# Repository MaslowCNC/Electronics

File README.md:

# Maslow PCBs

The printed circuit board which powers the Maslow CNC Machine

======================

Layout

Schematic

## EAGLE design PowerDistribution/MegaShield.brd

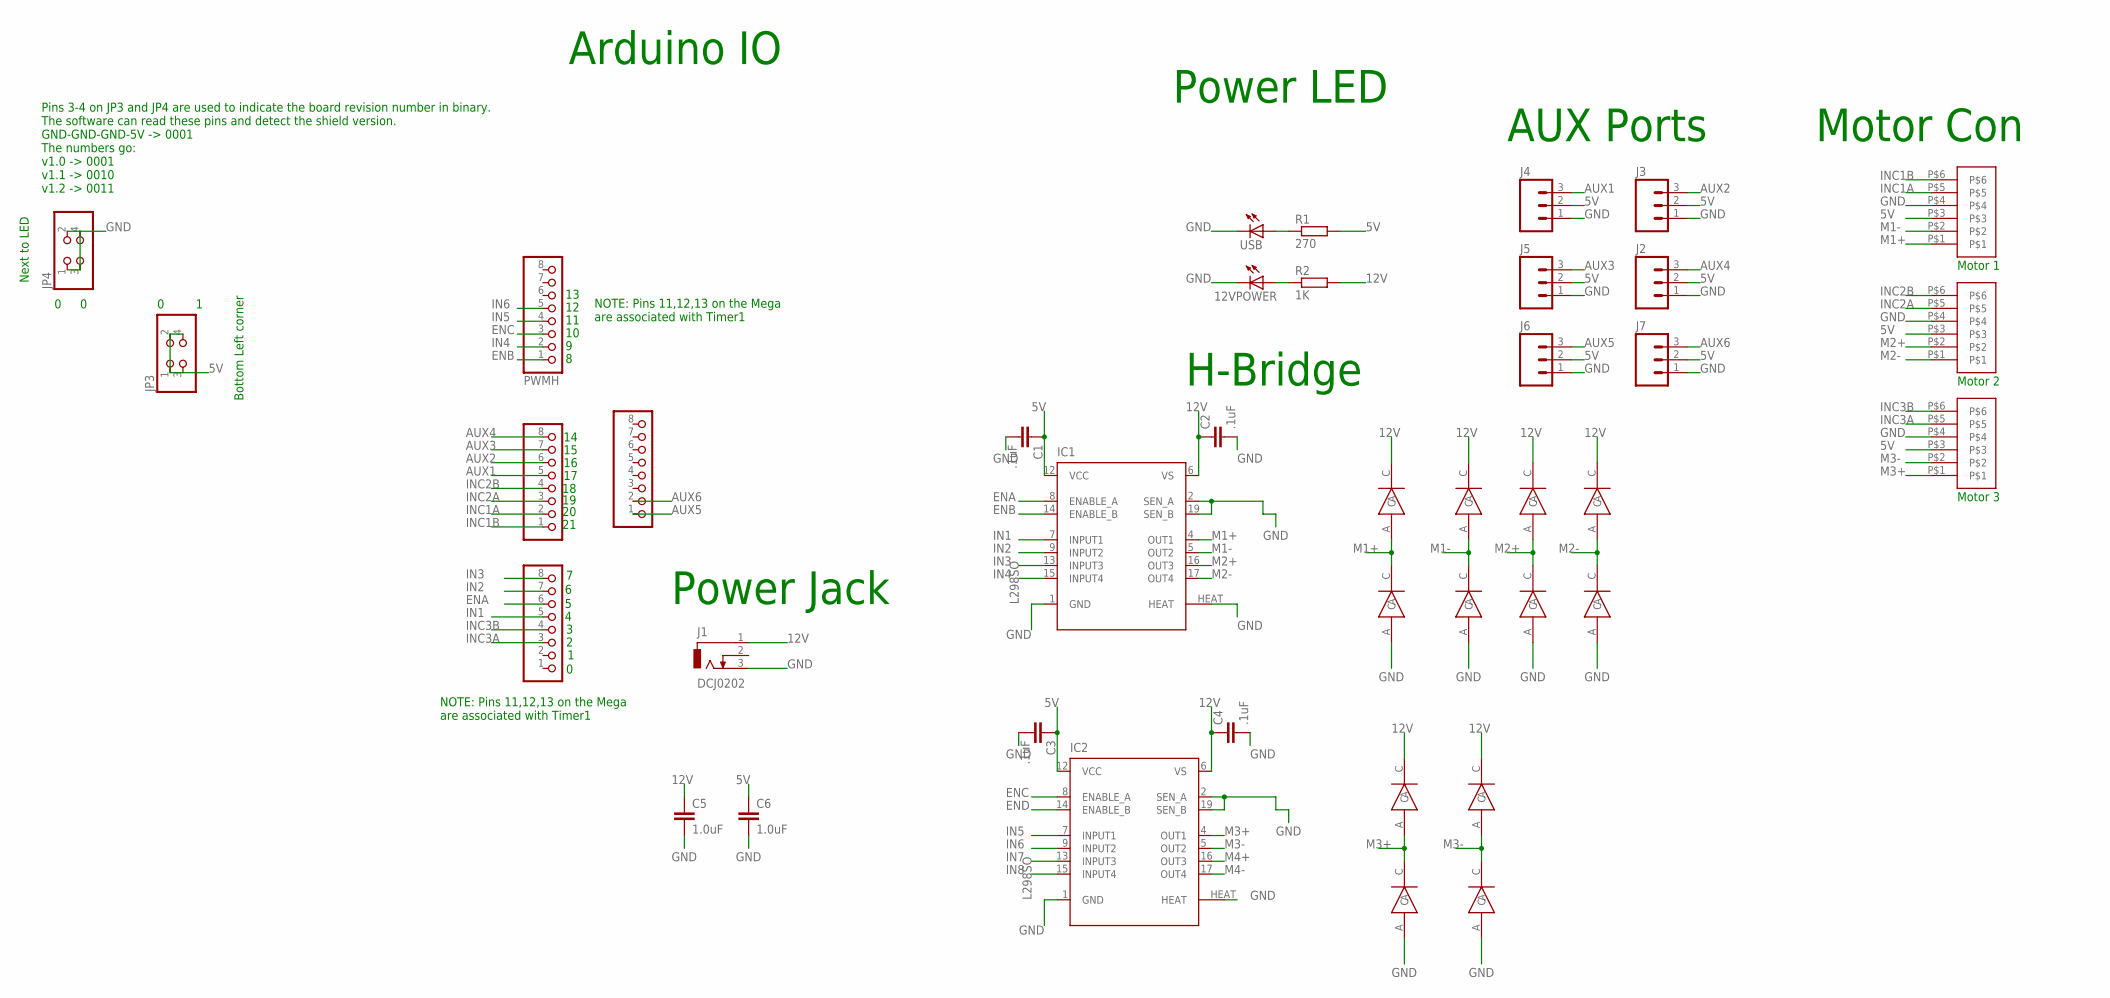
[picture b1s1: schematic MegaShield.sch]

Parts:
12VPOWER: LED_E; LED_1206
C1, C2, C3, C4: .1uF; C0805
C5, C6: 1.0uF; 0805-CAP
COMMUNICATION, COMMUNICATION1: PINHD-1X8; 1X08
IC1, IC2: L298SO; POWERSO-20
J1: DCJ0202
J2, J3, J4, J5, J6, J7: M03LOCK; 1X03_LOCK
JP3, JP4: PINHD-2X2; 2X02
PWMH: PINHD-1X8; 1X08
PWML: PINHD-1X8; 1X08
R1: 270; R0805
R2: 1K; R0805
U$1, U$12, U$20: JST-PH-6; JST-PHR-6-SMD
U$2, U$3, U$4, U$5, U$6, U$7, U$8, U$9, U$10, U$11, U$13, U$14: MRA4004; SMA
USB: LED_E; LED_1206

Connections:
5V: C1.1, C3.1, C6.1, IC1.12 (VCC), IC2.12 (VCC), J2.2, J3.2, J4.2, J5.2, J6.2, J7.2, JP3.1, JP3.2, JP3.3, JP3.4, R1.2, U$1.P$3, U$12.P$3, U$20.P$3
12V: C2.1, C4.1, C5.1, IC1.6 (VS), IC2.6 (VS), J1.1, R2.2, U$2.C, U$3.C, U$5.C, U$7.C, U$9.C, U$13.C
AUX1: COMMUNICATION.5, J4.3
AUX2: COMMUNICATION.6, J3.3
AUX3: COMMUNICATION.7, J5.3
AUX4: COMMUNICATION.8, J2.3
AUX5: COMMUNICATION1.1, J6.3
AUX6: COMMUNICATION1.2, J7.3
ENA: IC1.8 (ENABLE_A), PWML.6
ENB: IC1.14 (ENABLE_B), PWMH.1
ENC: IC2.8 (ENABLE_A), PWMH.3
END: IC2.14 (ENABLE_B)
GND: 12VPOWER.C, C1.2, C2.2, C3.2, C4.2, C5.2, C6.2, IC1.1 (GND), IC1.2 (SEN_A), IC1.19 (SEN_B), IC1.HEAT, IC2.1 (GND), IC2.2 (SEN_A), IC2.19 (SEN_B), IC2.HEAT, J1.3, J2.1, J3.1, J4.1, J5.1, J6.1, J7.1, JP4.1, JP4.2, JP4.3, JP4.4, U$1.P$4, U$4.A, U$6.A, U$8.A, U$10.A, U$11.A, U$12.P$4, U$14.A, U$20.P$4, USB.C
IN1: IC1.7 (INPUT1), PWML.5
IN2: IC1.9 (INPUT2), PWML.7
IN3: IC1.13 (INPUT3), PWML.8
IN4: IC1.15 (INPUT4), PWMH.2
IN5: IC2.7 (INPUT1), PWMH.4
IN6: IC2.9 (INPUT2), PWMH.5
IN7: IC2.13 (INPUT3)
IN8: IC2.15 (INPUT4)
INC1A: COMMUNICATION.2, U$1.P$5
INC1B: COMMUNICATION.1, U$1.P$6
INC2A: COMMUNICATION.3, U$12.P$5
INC2B: COMMUNICATION.4, U$12.P$6
INC3A: PWML.3, U$20.P$5
INC3B: PWML.4, U$20.P$6
M1+: IC1.4 (OUT1), U$1.P$1, U$3.A, U$4.C
M1-: IC1.5 (OUT2), U$1.P$2, U$5.A, U$6.C
M2+: IC1.16 (OUT3), U$7.A, U$8.C, U$12.P$2
M2-: IC1.17 (OUT4), U$9.A, U$10.C, U$12.P$1
M3+: IC2.4 (OUT1), U$2.A, U$11.C, U$20.P$1
M3-: IC2.5 (OUT2), U$13.A, U$14.C, U$20.P$2
M4+: IC2.16 (OUT3)
M4-: IC2.17 (OUT4)
unnamed: R1.1, USB.A
unnamed: 12VPOWER.A, R2.1

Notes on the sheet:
Motor 1
Motor 2
H-Bridge
Power LED
Power Jack
Arduino IO
AUX Ports
Motor Con
Motor 3
Pins 3-4 on JP3 and JP4 are used to indicate the board revision number in binary. The software can read these pins and detect the shield version. GND-GND-GND-5V -> 0001 The numbers go: v1.0 -> 0001 v1.1 -> 0010 v1.2 -> 0011
NOTE: Pins 11,12,13 on the Mega are associated with Timer1
Next to LED
Bottom Left corner

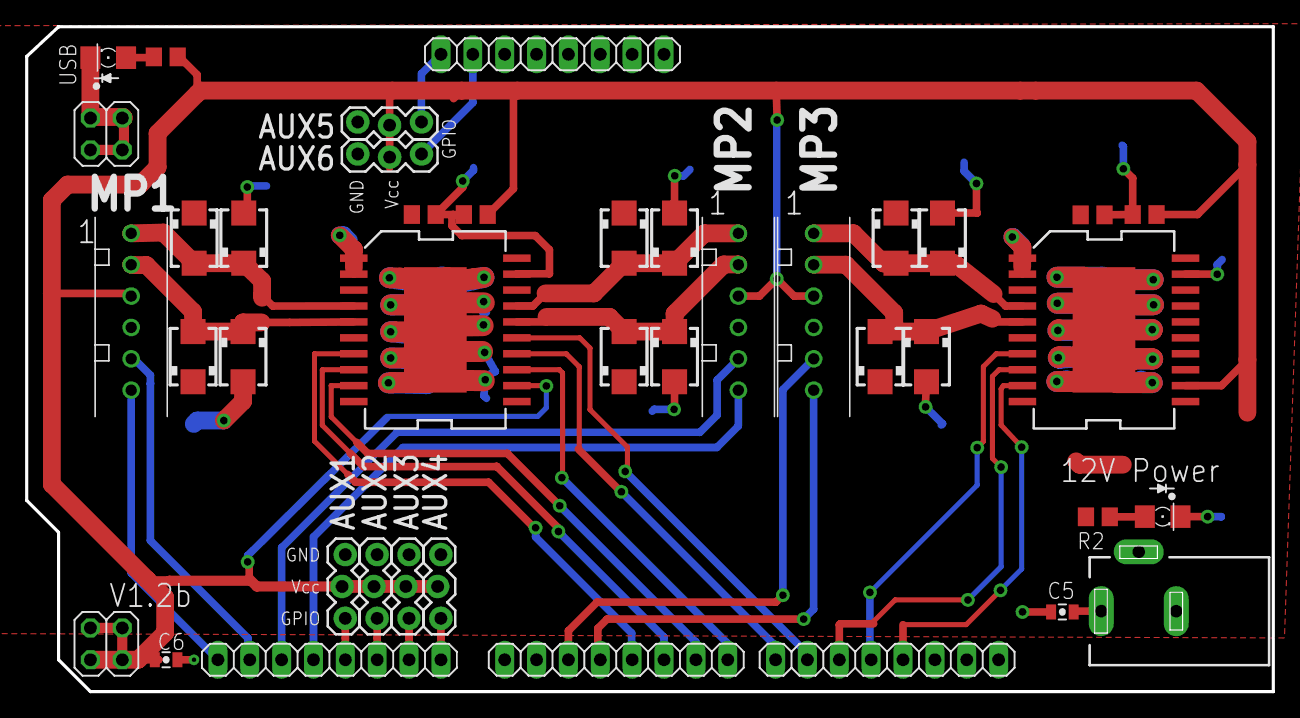
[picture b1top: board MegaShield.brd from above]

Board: 2 copper layers, 99.4 x 53.0 mm, 40 parts (0 on the bottom side), 32 nets.

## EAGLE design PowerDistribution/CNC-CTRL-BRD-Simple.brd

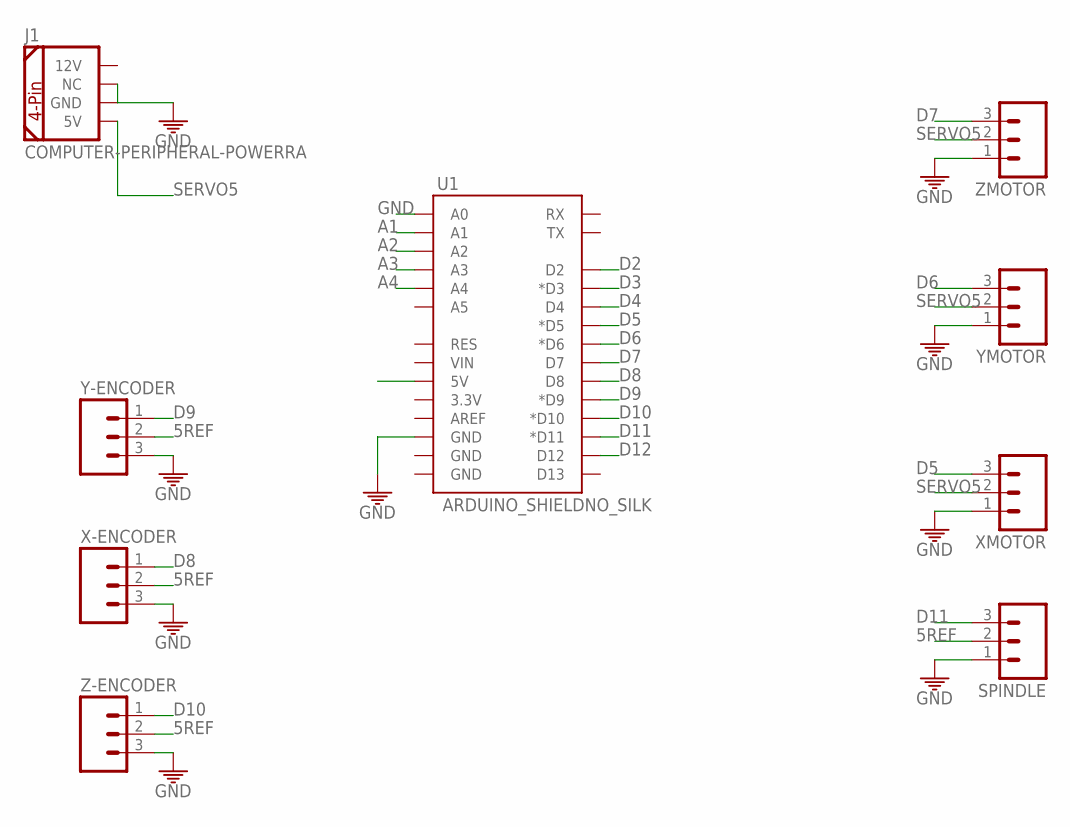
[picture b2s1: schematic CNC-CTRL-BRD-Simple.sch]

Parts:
J1: COMPUTER-PERIPHERAL-POWERRA; COMPUTER-PERIPHERAL-POWER-RA
SPINDLE: M03LOCK; 1X03_LOCK
U1: ARDUINO_SHIELDNO_SILK; DUEMILANOVE_VIAS
X-ENCODER: M03LOCK; 1X03_LOCK
XMOTOR: M03LOCK; 1X03_LOCK
Y-ENCODER: M03LOCK; 1X03_LOCK
YMOTOR: M03LOCK; 1X03_LOCK
Z-ENCODER: M03LOCK; 1X03_LOCK
ZMOTOR: M03LOCK; 1X03_LOCK

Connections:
5REF: SPINDLE.2, U1.5V, X-ENCODER.2, Y-ENCODER.2, Z-ENCODER.2
A1: U1.A1
A2: U1.A2
A3: U1.A3
A4: U1.A4
D2: U1.D2
D3: U1.D3 (*D3)
D4: U1.D4
D5: U1.D5 (*D5), XMOTOR.3
D6: U1.D6 (*D6), YMOTOR.3
D7: U1.D7, ZMOTOR.3
D8: U1.D8, X-ENCODER.1
D9: U1.D9 (*D9), Y-ENCODER.1
D10: U1.D10 (*D10), Z-ENCODER.1
D11: SPINDLE.3, U1.D11 (*D11)
D12: U1.D12
GND: J1.GND, J1.NC, SPINDLE.1, U1.A0, U1.GND@2 (GND), X-ENCODER.3, XMOTOR.1, Y-ENCODER.3, YMOTOR.1, Z-ENCODER.3, ZMOTOR.1
SERVO5: J1.5V, XMOTOR.2, YMOTOR.2, ZMOTOR.2

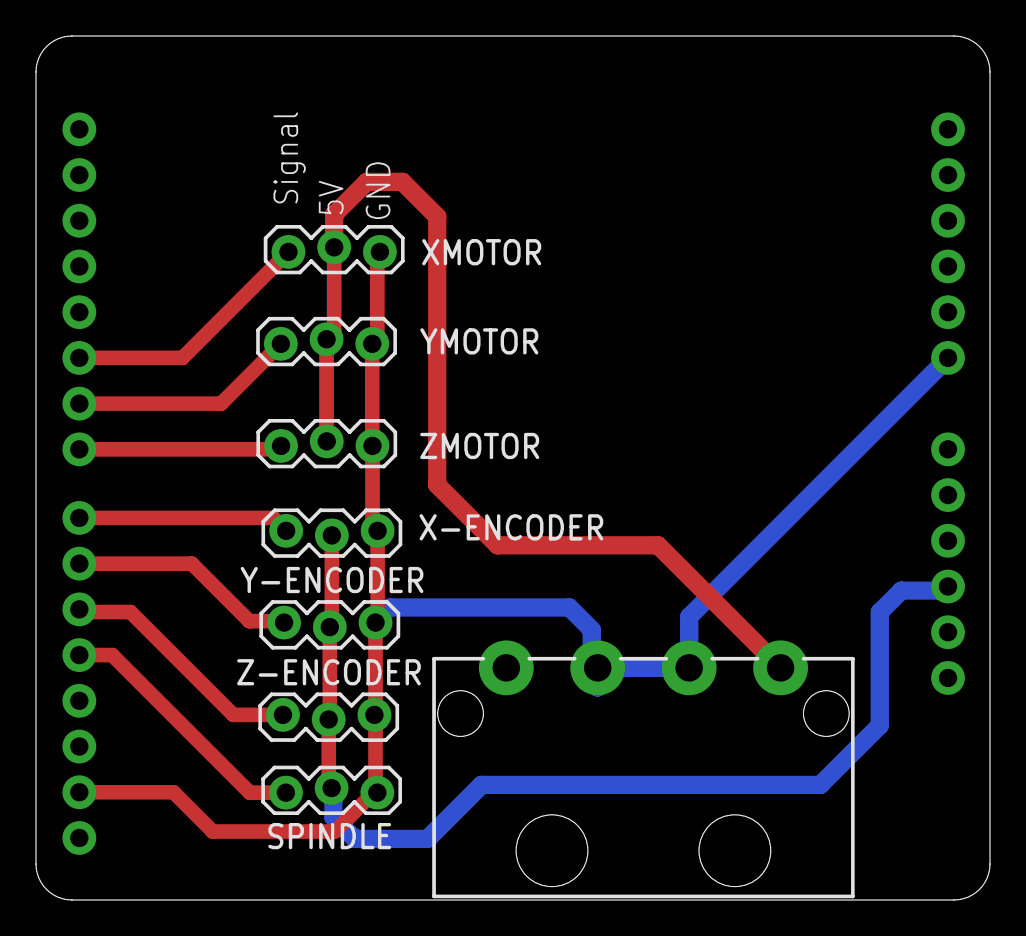
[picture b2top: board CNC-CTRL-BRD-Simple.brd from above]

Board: 2 copper layers, 53.0 x 48.0 mm, 9 parts (0 on the bottom side), 10 nets.

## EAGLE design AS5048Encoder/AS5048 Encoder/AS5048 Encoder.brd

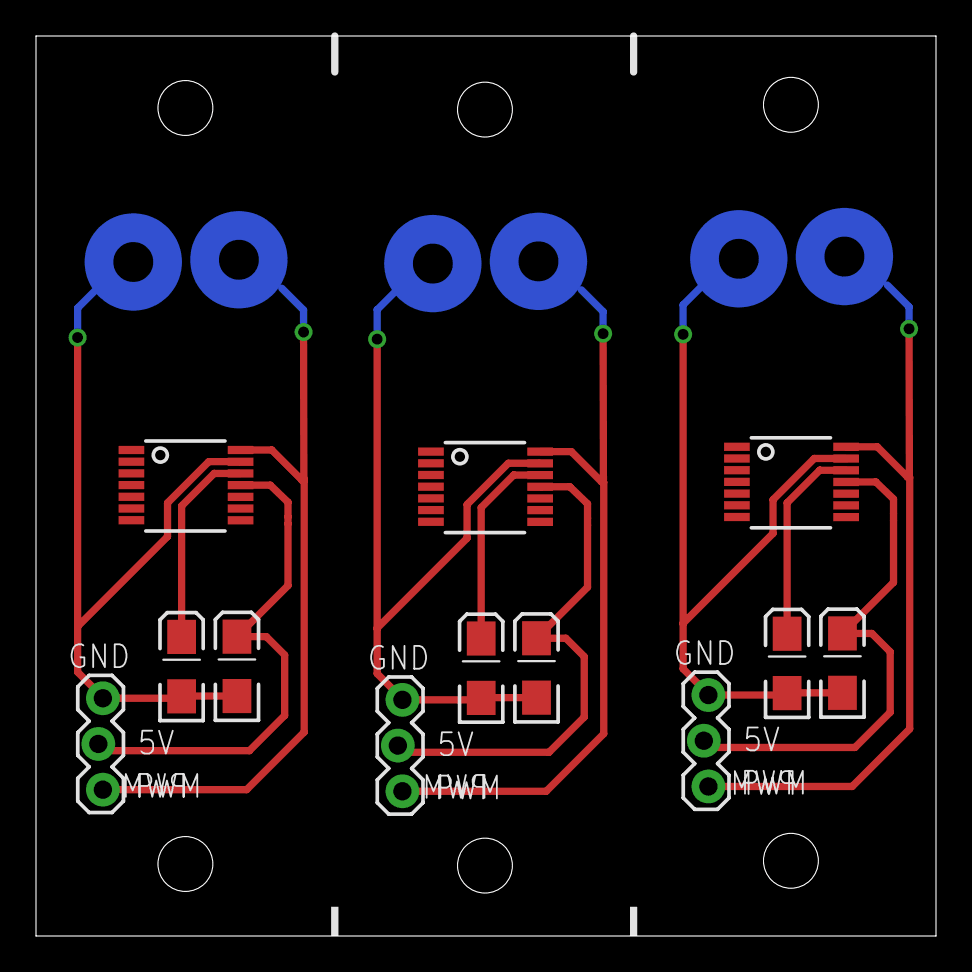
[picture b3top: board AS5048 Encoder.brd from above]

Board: 2 copper layers, 50.0 x 50.0 mm, 18 parts (0 on the bottom side), 12 nets.

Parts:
C1, C3, C5: 100nF; EIA3216-KIT
C2, C4, C6: 10uF; EIA3216-KIT
JP1, JP2, JP3: 1X03_LOCK
U$1, U$4, U$7: AS5048; TSOP14
U$2, U$3, U$5, U$6, U$8, U$9: STAND-OFF-TIGHT

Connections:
3V1: C2.A, U$4.12
3V2: C6.A, U$7.12
3V3: C4.A, U$1.12
GND: C3.C, C4.C, JP1.1, U$1.13
GND1: C1.C, C2.C, JP2.1, U$4.13
GND2: C5.C, C6.C, JP3.1, U$7.13
PWM: JP1.3, U$1.14
PWM1: JP2.3, U$4.14
PWM2: JP3.3, U$7.14
VCC: C3.A, JP1.2, U$1.11
VCC1: C1.A, JP2.2, U$4.11
VCC2: C5.A, JP3.2, U$7.11

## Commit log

2015-01-29 Added pictures of schematics and layouts
2016-07-12 added docs
2016-08-19 outline in
2016-08-19 ethernet jacks in
2016-08-20 coming along
2016-08-20 hbridge in
2016-08-20 switch to check LED colors
2016-08-20 shipped here
2016-08-20 commit to switch branches
2016-08-29 stash
2016-08-30 started, stopped because not a priority
2016-10-24 revision 2 shipped here
2016-10-24 switched polarity on DC jack
2016-11-03 Added BOM
2016-11-04 cleanup and update pictures
2016-11-04 add labels to schematic
2016-11-04 Really added label to schematic
2016-11-04 put picture in readme
2016-11-04 added schematic to readme
2016-11-15 added aux ports
2016-11-20 smd L298
2016-11-20 before move
2016-11-20 end of night
2016-11-20 routing
2016-11-20 2 axis done
2016-11-20 duplicate schematic elements
2016-11-20 parts placed
2016-11-22 routed, not checked
2016-11-22 added aux 5 and aux 6
2016-11-30 put in top header for stability
2016-11-30 add second indicator line to connectors
2016-12-01 started moving things
2016-12-01 shifting and routing
2016-12-01 routed v1
2016-12-08 add missing wire
2016-12-08 route
2016-12-08 change diode placement
2016-12-29 update documentation pictures
2016-12-29 updated documention pictures
2016-12-29 updated documentation pictures again
2016-12-29 add binary board revision #
2016-12-29 put headers on grid
2016-12-29 add polarity indicator to LED
2016-12-29 diodes all the same direction
2016-12-29 moved up but not re-routed
2016-12-29 re-routed
2016-12-29 much clean up
2016-12-29 wire up 4th axis encoder
2016-12-29 a little more DRC, shipped here
2017-01-12 clean up for PCB production
2017-01-12 maybe something not saved?
2017-01-13 update BOM
2017-02-04 Tie broken power connection
2017-02-06 swap encoder pins around
2017-02-06 everything lines up
2017-02-06 everything ripped up
2017-02-06 still ripped up, all pins shifted
2017-02-06 shifted down and over
2017-02-07 looks good except for residual holes under L298s
2017-02-07 builds but not checked yet
2017-02-07 CAM generated
2017-02-07 move logo
2017-02-07 redo CAM
2017-02-07 add .1uf to cap description
2017-03-15 Add documentation pictures
2017-04-01 add motor port numbers and 12v LED
2017-04-02 remove forth axis
2017-04-02 ship here
2017-06-02 update pictures
2017-06-06 Increase schematic resolution
2017-06-30 Update BOM.txt
    Still missing P/N for power supply.
2017-07-01 Added Power Supply and Arduino
2017-07-17 Update documentation pictures and clean up
2017-08-21 Identify pin1 on connectors MP1, MP2, MP3
2017-09-13 Chip 1 moved over
2017-09-13 more routing done
2017-09-13 All parts routed
2017-09-13 Everything Routed?
2017-09-13 finished?
2017-09-28 Update board version detection system
2017-09-29 Clean up the pin 2/3 spacing
2017-10-30 Update power connnector on BOM
2017-11-09 fix issue with not recognizing board
2017-11-09 really fix issue with detecting board number and clean up documentation so it won't happen again
2017-11-10 auto save
2017-11-10 auto save again
2017-11-10 Put pin 1 indicator back in the right spot
2017-11-10 Update schematic and board images
2017-11-17 Add all datasheets
2017-12-20 Add datasheet for z-axis motor
    As requested in https://forums.maslowcnc.com/t/z-axis-motor-specs/340/20
2017-12-25 address issue #37
    EaglsCAD .do file incorrectly identified as Stata language by github/linguist.
    Use .gitattributes file to override detection by markiing the file as 'generated code'.
2018-01-12 Address Various Issues
    Correct Schematic - Issue#36
    Indicate LED polarity - Issue#22
    Add equivalent Heatsink to BOM - Issue#18
2018-01-12 Add Heatsink part number to BOM
    This Mouser part number is slightly shorter, but available in single quantities and costs less than $3:
    Mouser-532-374124B35G
    https://www.mouser.com/productdetail/aavid-thermalloy/374124b00035g?qs=sGAEpiMZZMttgyDkZ5WiulSjpO3gDOKQ4Eu1ZE9AH98%3D
2018-01-12 Add diode indicators per Issue#22, change net names per Issue#36
2018-01-12 Clean out unneeded EAGLE files
    Remove the '.b#x', ',s#x', '.do', '.dri', '.gpi', and '.scr' files which EAGLE leaves behind. They are not needed for others to use the '.brd' and '.sch' files
2018-01-12 Add gitignore for EAGLE files
    Ignore EAGLE backup, project, autorouter, CAM and lock files.
2018-01-14 Change value of R2, clean out old version of schematic
    R2 value changed to 1K per Issue #45. Schematic and BOM updated.
    Remove an old .sch file overlooked in previous housecleaning.
    Watch to see that gitignore correctly ignores the '.b#x' and '.s#x' files
2018-01-14 Add caps to 12V and 5V lines
    Board Layout: C5 next to 12V jack J1, C6 next to JP3 bottom left corner.
    Schematic updated
    BOM updated
    Note: branch descended from PR#48, as it uses the schematic and board files from that PR.
2018-03-14 add main picture
2018-03-23 add bom and instructions
2018-03-23 Convert BOM to be markdown
2018-03-23 change links to be absolute
2018-03-23 try raw link for image
2018-03-23 change picture path to be the raw vers
2018-04-14 update attach motors picture to remove labels fro
2018-06-04 Add robot file
2018-06-04 Add instructions file
2018-06-04 fix image links
2018-06-04 update main picture
2021-04-17 feat: Adds initial kitspace files to test
2021-04-19 Remove dead link
2021-04-26 Add Gerber Files
    Gerber File exported from Eagle
2021-04-26 Convert Eagle to KiCad
2021-05-01 feat: Adds gerbers to kitspace.yml
2021-05-01 fix: Corrects Gerbers folder in kitspace.yml

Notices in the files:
parts and their libraries:
SparkFun-Passives: Licensing: CC v3.0 Share-Alike You are welcome to use this library for commercial purposes.
SparkFun-Connectors: Licensing: Creative Commons ShareAlike 4.0 International - https://creativecommons.org/licenses/by-sa/4.0
